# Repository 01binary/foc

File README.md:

# Field-Oriented Control Drive

A board that controls BLDC motors in robot joints, based on [SimpleFOC Drive Shield](https://github.com/simplefoc/SimpleFOC-DriveShield).

|Feature|Description|
|-|-|
|Current|`20A` continuous, `30A` peak, `75A` max|
|Voltage|`30V` max|
|Encoders|[AS5047D](https://www.digikey.com/en/products/detail/ams-osram-usa-inc/as5047d-atst-tssop14-lf-t-rdp/4896031) (Onboard), [ASKIM2](https://www.rls.si/eng/aksim-2-off-axis-rotary-absolute-encoder) (External)|
|Driver|[DRV8320HRTVT](https://www.digikey.com/en/products/detail/texas-instruments/drv8320hrtvt/7426985) Triple Half-Bridge Gate Driver|
|Communication|[MCP2562FDT-E/MF](https://www.mouser.com/en/ProductDetail/Microchip-Technology/MCP2562FDT-E-MF) CAN-FD Transceiver|
|Power|`12V` from [XT60PW-F](https://www.aliexpress.us/item/3256808202387933.html)|

## Microcontroller

This board uses [STM32G474RBT3](https://www.digikey.com/en/products/detail/stmicroelectronics/STM32G474RBT3/10326726) MCU.

|Specification|Value|
|-|-|
|Power|`3.3V`|
|Memory|`512 KB` Flash, `96 KB` SRAM|
|ADC|5x `12-bit` ADC, up to `16-bit`|
|DAC|7x `12-bit` DAC|
|Timers|17x|
|Interfaces|`CAN-FD`, `I2C`, `UART`, `SPI`, `USB 2.0`|
|Capabilities|`CORDIC` for Trigonometric Function, `FMAC` Filter Mathematical Accelerator|

## Motor Driver

The [DRV8320HRTVT](https://www.digikey.com/en/products/detail/texas-instruments/drv8320hrtvt/7426985) Triple Half-Bridge Gate Driver with Hardare interface is used to drive three N-channel power MOFSETs.

+ `1.8V`, `3.3V`, and `5V` Logic Inputs
+ Adjustable Slew Rate Control
+ Up to 100% PWM Duty Cycle
+ High-Side Charge Pump
+ Low-SIde Linear Regulator
+ `4V` to `6 V` Operating Voltage
+ `0.8mA` to `600mA` Output Capability

## MOSFETs

The [BSZ0904NSI](https://www.lcsc.com/datasheet/C51908785.pdf) `30V` `60A` N-channel power MOSFETs are used to drive a single 3-phase brushless DC motor.

## Current Sense

Current is sensed by using the [3-Shunt, Amplified Current Sensing](https://wiki.st.com/stm32mcu/wiki/STM32MotorControl:Motor_Control_Boards_Description#Motor-phase-current-sensing) scheme from STM32 user guide:

|Component|Description|
|-|-|
|[HoJLR2512-3W-2mR-1%](https://jlcpcb.com/partdetail/Milliohm-HoJLR2512_3W_2mR_1/C2903471)|`2mΩ` `3W` Current Sense Resistor SMD ±1% 2512 Current Sense Resistors / Shunt Resistors|
|[INA240A1PWR](https://jlcpcb.com/partdetail/TexasInstruments-INA240A1PWR/C93965)|Op-Amps|

## Encoders

The board supports dual encoders:

+ AS5047D on the motor (before gearbox)
+ ASKIM-2 mounted on the drive (after gearbox)

### Onboard Encoder

The onboard AS5047D high-resolution encoder with `SPI` interface is mounted on the board:

|Pin|Signal|
|-|-|
|1|`CS`|
|2|`CLK`|
|3|`MISO`|
|4|`MOSI`|
|11|`5V`|

### External Encoder

The external absolute AKSIM-2 encoder with `SPI` interface uses a 10-pin FCI connector:

|Pin|Signal|
|-|-|
|1|`5V`|
|2|`GND`|
|3|External Temperature Sensor Pin 1 (Pass-Thru)|
|4|External Temperature Sensor Pin 2 (Pass-Thru)|
|5|`SCK`|
|6|`CS`|
|7|`MISO`|
|8|`MOSI`|

## Pin Mapping

|Pin|Net|
|-|-|
|`VBAT`|`+3.3V`|
|`PC13`|Status LED|
|`OSC32_IN`|`32.768kHz` Crystal Oscillator In|
|`OSC32_OUT`|`32.768kHz` Crystal Oscillator Out|
|`OSC_IN`|`8MHz` Crystal Oscillator In|
|`OSC_OUT`|`8Mhz` Crystal Oscillator Out|
|`RESET`|ARM JTAG Programmer Reset Pin|

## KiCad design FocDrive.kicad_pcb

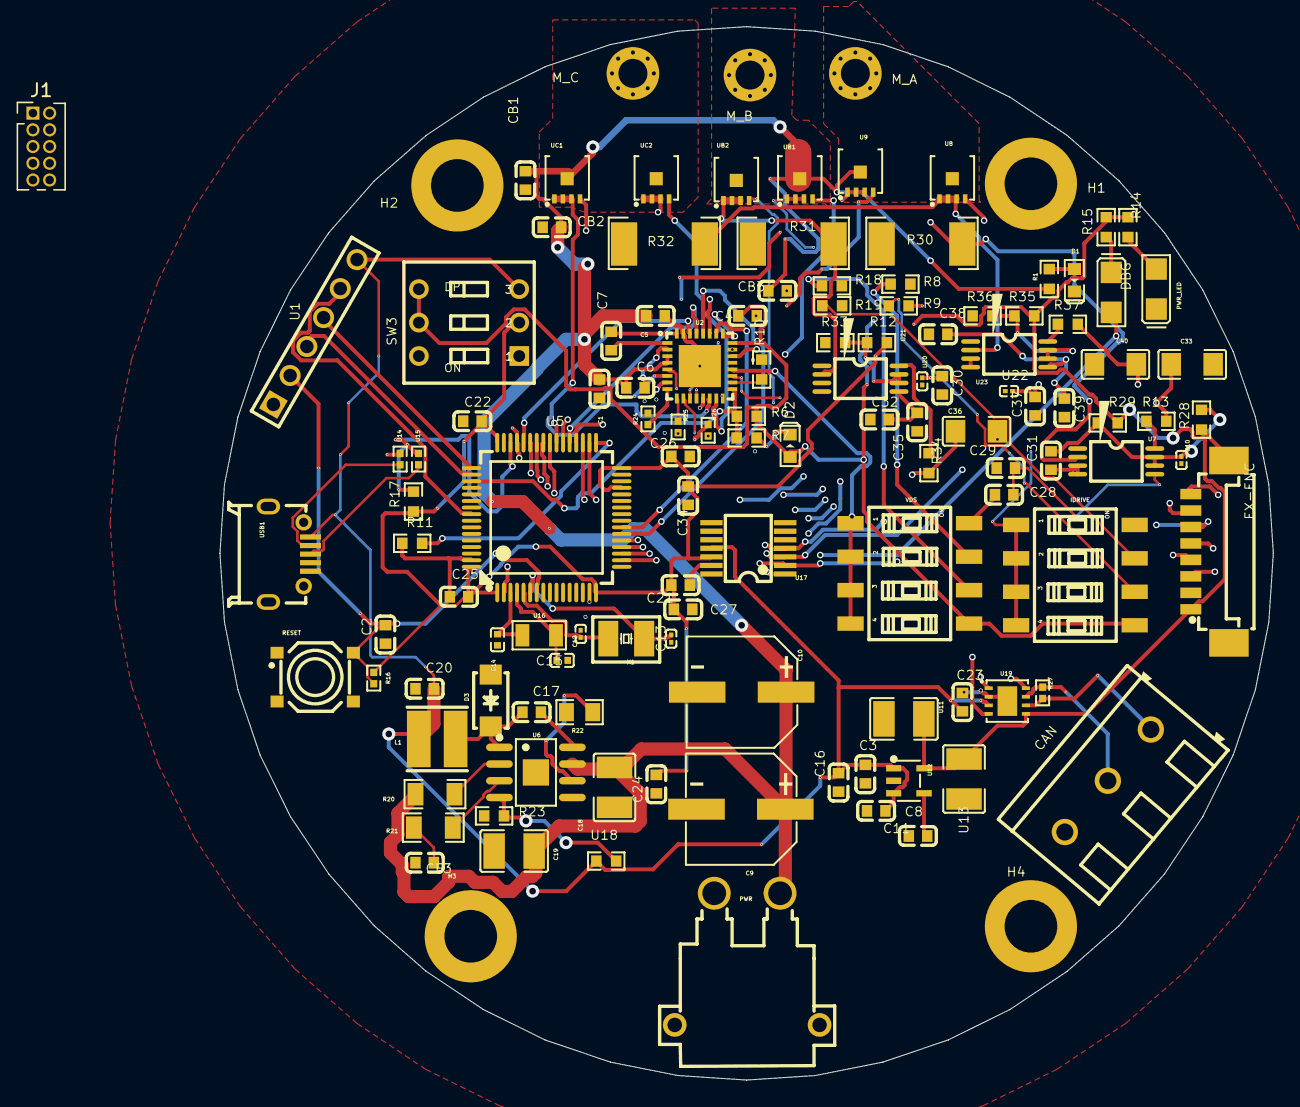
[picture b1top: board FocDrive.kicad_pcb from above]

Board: 4 copper layers, 80.0 x 80.0 mm, 125 parts (0 on the bottom side), 85 nets.

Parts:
C1, C5: C0603B104K160NT; C0603
C2, C3, C4, C6, C8, C21, C30, C31, C37: 1uF; C0603
C7: 47nF; C0603
C9, C10: 220uF; CAP-SMD_BD8.0-L8.3-W8.3-LS9.5-FD
C11: 22nF; C0603
C12, C13: 20pF; C0201
C14, C15: 18pF; C0402
C16, C17, C22, C23, C24, C25, C26, C27, C28, C29, C32, C35, C38, C39: 100nF; C0603
C18, C19: 10uF; C1210
C20: 47uF; C0603
C33, C36, C40: 2.2nF; C1206
C34: 10nF; C0603
CAN: WJ500V-5.08; CONN-TH_3P-P5.00_WJ500V-5.08-3P
CB1, CB2, CB3: C0603B104K160NT; C0603
CF3: 1nF; C0603
D1, D2: LED-0603_R; LED0603_RED
D3: SS14; SMA_L4.2-W2.6-LS5.0-RD_1
DBG: LC150LGCT; LED1206-RD
EX-ENC: 10114830-11108LF; CONN-SMD_8P-P1.25_AMPHENOL_10114830-11108LF
H1, H2, H3, H4: HOLEHOLE COPY; HOLEHOLE
IDRIVE: 2.54-4P TPGT; SW-SMD_8P-L10.2-W6.2-P2.54-LS9.4
J1: Conn_ARM_JTAG_SWD_10; PinHeader_2x05_P1.27mm_Vertical
L1: 2.2UH,20%; IND-SMD_L4.0-W4.0_C9900022260
M_A: M2 PLATED HOLE WITH MINI HOLES
M_B: M2 PLATED HOLE WITH MINI HOLES
M_C: M2 PLATED HOLE WITH MINI HOLES
PWR: XT30PW-M; CONN-TH_XT30PW-M
PWR_LED: LC150LGCT; LED1206-RD
R1, R6, R7: 4.7k; R0603
R8, R19: 75k; R0603
R9, R18: 18k; R0603
R10: 47k; R0603
R11, R17: 4.7kΩ; R0603
R12, R28, R29, R33, R35, R36: 10kΩ; R0603
R13, R34, R37: 100Ω; R0603
R14, R15: 510Ω; R0603
R16: 10kΩ; R0402
R20, R21: 100kΩ; R1206
R22: 250kΩ; R0805
R23: 22kΩ; R0603
R24, R25, R26: 0Ω; R0402
R27: 120Ω; R0402
R30, R31, R32: 2mΩ; RES-SMD_L6.4-W3.2-R2512
RESET: HX 5.2X5.2X1.5H SWITCH TACTILE; SW-SMD_4P-L5.2-W5.2-P3.7-LS6.4-1
SW3: KH-BM2.54-3P; SW-TH_KH-BM2.54-3P
U1: HC-PM254-8.5H-1X6PZ; HDR-TH_HC-PM254-8.5H-1X6PZ
U2: DRV8320HRTVT; WQFN-32_L5.0-W5.0-P0.50-TL-EP
U5: STM32G474RBT3; LQFP-64_L10.0-W10.0-P0.50-LS12.0-BL
U6: MP1584EN-LF-Z; SOIC-8_L5.0-W4.0-P1.27-LS6.0-BL-EP2.0
U7, U21, U23: INA240A1PWR; TSSOP-8_L4.4-W3.0-P0.65-LS6.4-BL
U8, U9: BSZ0901NSATMA1; DFN-8_L3.3-W3.3-P0.65-BL-2
U10, U20, U22: 100nF; C0201
U11, U13: 10uF; C1210
U12: RT9193-33GB; SOT-23-5_L3.0-W1.7-P0.95-LS2.8-BL
U14, U15: 20Ω; R0402
U16: 32.768kHz; CRYSTAL-SMD_L3.2-W1.5-1
U17: AS5047D-ATSM; TSSOP-14_L5.0-W4.4-P0.65-LS6.4-BL
U18: 118kΩ; R0603
U19: MCP2562FDT-E/MF; DFN-8_L3.0-W3.0-P0.65-BL-EP
UB1, UB2: BSZ0901NSATMA1; DFN-8_L3.3-W3.3-P0.65-BL-2
UC1, UC2: BSZ0901NSATMA1; DFN-8_L3.3-W3.3-P0.65-BL-2
USB1: HX USB-MICR XNJ ZB; MICRO-USB-SMD_HX-USB-MICRO-XNJ-JB
VDS: 2.54-4P TPGT; SW-SMD_8P-L10.2-W6.2-P2.54-LS9.4
X1: 8MHz; CRYSTAL-SMD_L3.2-W2.5_3225-8MHZ

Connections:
$1N2: D1.1, R1.1
$1N29: C7.1, U2.32
$1N30: C7.2, U2.1
$1N32: C6.2, U2.2
$1N71: PWR_LED.2, R14.1
$1N76: DBG.1, R15.1
$1N85: C11.2, U12.4
$1N91: U14.1, USB1.2
$1N92: U15.1, USB1.3
$1N109: R18.1, VDS.6
$1N110: R8.1, VDS.7
$1N111: IDRIVE.6, R9.1
$1N112: IDRIVE.7, R19.1
$1N122: R20.2, U6.2
$1N125: C17.2, U6.8
$1N126: C17.1, D3.1, L1.2, U6.1
$1N127: R23.2, U6.4, U18.2
$1N128: R21.2, U6.3
$1N130: CF3.1, R21.1
$1N134: R22.2, U6.6
$1N158: CAN.3, R27.2, U19.6
$1N159: CAN.2, R27.1, U19.7
$1N209: C28.2, C29.2, U7.5
$1N211: C31.2, R28.2, R29.1, U7.6, U7.7, U10.2
$1N213: R13.1, U7.8
$1N225: C30.2, R12.1, R33.2, U20.2, U21.6, U21.7
$1N230: R34.1, U21.8
$1N233: C32.2, C35.2, U21.5
$1N236: C37.2, R35.1, R36.2, U22.2, U23.6, U23.7
$1N241: R37.1, U23.8
$1N244: C38.2, C39.2, U23.5
$1N3452: D2.2, R7.2
+3.3V: C21.2, C22.2, C24.2, C25.2, C26.2, C27.2, C34.2, EX-ENC.1, J1.1 (VTref), R12.2, R14.2, R15.2, R16.2, R17.1, R29.2, R35.2, SW3.2, U5.1, U5.16, U5.29, U5.32, U5.48, U5.64, U11.2, U12.5, U13.2, U17.12, U19.5
+5V: C3.2, C8.2, C16.2, C20.2, C23.2, L1.1, SW3.3, U1.6, U12.1, U12.3, U17.11, U18.1, U19.3, USB1.1
CS: U5.18, U17.1
CS2: EX-ENC.6, U5.42
DVDD: C4.2, D2.1, IDRIVE.5, R6.2, R9.2, SW3.4, SW3.5, U2.24, VDS.5
ENABLE: R11.2, U2.22, U5.33
GHA: U2.5, U9.4
GHB: U2.12, UB1.4
GHC: U2.13, UC1.4
GLA: U2.7, U8.4
GLB: U2.10, UB2.4
GLC: U2.15, UC2.4
GND: C1.1, C2.1, C3.1, C4.1, C5.1, C8.1, C9.2, C10.2, C11.1, C12.1, C13.1, C14.1, C15.1, C16.1, C18.1, C19.1, C20.1, C21.1, C22.1, C23.1, C24.1, C25.1, C26.1, C27.1, C28.1, C29.1, C30.1, C31.1, C32.1, C33.1, C34.1, C35.1, C36.1, C37.1, C38.1, C39.1, C40.1, CAN.1, CB1.2, CB2.1, CB3.2, CF3.2, D1.2, D3.2, EX-ENC.2, EX-ENC.9, EX-ENC.10, IDRIVE.8, J1.3 (GND), J1.5 (GND), J1.9 (GNDDetect), PWR.1, PWR_LED.1, R8.2, R10.2, R11.1, R18.2, R19.2, R22.1, R23.1, R24.2, R25.2, R26.2, R28.1, R30.1, R31.1, R32.1, R33.1, R36.1, RESET.4, U1.1, U2.23, U2.31, U2.33, U5.15, U5.27, U5.31, U5.47, U5.63, U6.5, U6.9, U7.3, U7.4, U10.1, U11.1, U12.2, U13.1, U17.5, U17.13, U19.2, U19.9, U20.1, U21.3, U21.4, U22.1, U23.3, U23.4, USB1.4, USB1.5, USB1.6, USB1.7, USB1.8, USB1.9, VDS.8
IDRIVE: IDRIVE.1, IDRIVE.2, IDRIVE.3, IDRIVE.4, U2.19
IN1+: R30.2, U7.2, UC2.1, UC2.2, UC2.3
IN2+: R31.2, U21.2, UB2.1, UB2.2, UB2.3
IN3+: R32.2, U8.1, U8.2, U8.3, U23.2
INHA: U2.25, U5.39
INHB: U2.27, U5.38
INHC: U2.29, U5.37
INLA: U2.26, U5.23
INLB: U2.28, U5.22
INLC: U2.30, U5.44
MISO: EX-ENC.7, U5.20, U17.3
MODE: R10.1, U2.18
MOSI: EX-ENC.8, U5.21, U17.4
NFLT: R6.1, R7.1, U2.17, U5.51
OSC1: C12.2, U5.5, X1.2
OSC2: C13.2, U5.6, X1.1
OSC3: C14.2, U5.3, U16.2
OSC4: C15.2, U5.4, U16.1
PA11: U5.45, U14.2, U19.4
PA12: R17.2, U5.46, U15.2, U19.1
PC13: DBG.2, U5.2
PHASE1: C33.2, R13.2, U5.36
PHASE2: C36.2, R34.2, U5.35
PHASE3: C40.2, R37.2, U5.34
RESET: C2.2, R16.1, RESET.2, U1.2, U5.7
SCK: EX-ENC.5, U5.19, U17.2
SHA: M_A.1, U2.6, U8.5, U9.1, U9.2, U9.3
SHB: M_B.1, U2.11, UB1.1, UB1.2, UB1.3, UB2.5
SHC: M_C.1, U2.14, UC1.1, UC1.2, UC1.3, UC2.5
SLA: R24.1, U2.8
SLB: R25.1, U2.9
SLC: R26.1, U2.16
STBY: U5.40, U19.8
SWCLK: U1.3, U5.50
SWDIO: U1.4, U5.49
SWO: U1.5, U5.56
TEMP1: EX-ENC.3, U5.43
TEMP2: EX-ENC.4, U5.41
VCC: C1.2, C5.2, C6.1, C9.1, C10.1, C18.2, C19.2, CB1.1, CB2.2, CB3.1, PWR.2, R1.2, R20.1, U2.3, U2.4, U6.7, U9.5, UB1.5, UC1.5
VDS: U2.20, VDS.1, VDS.2, VDS.3, VDS.4
